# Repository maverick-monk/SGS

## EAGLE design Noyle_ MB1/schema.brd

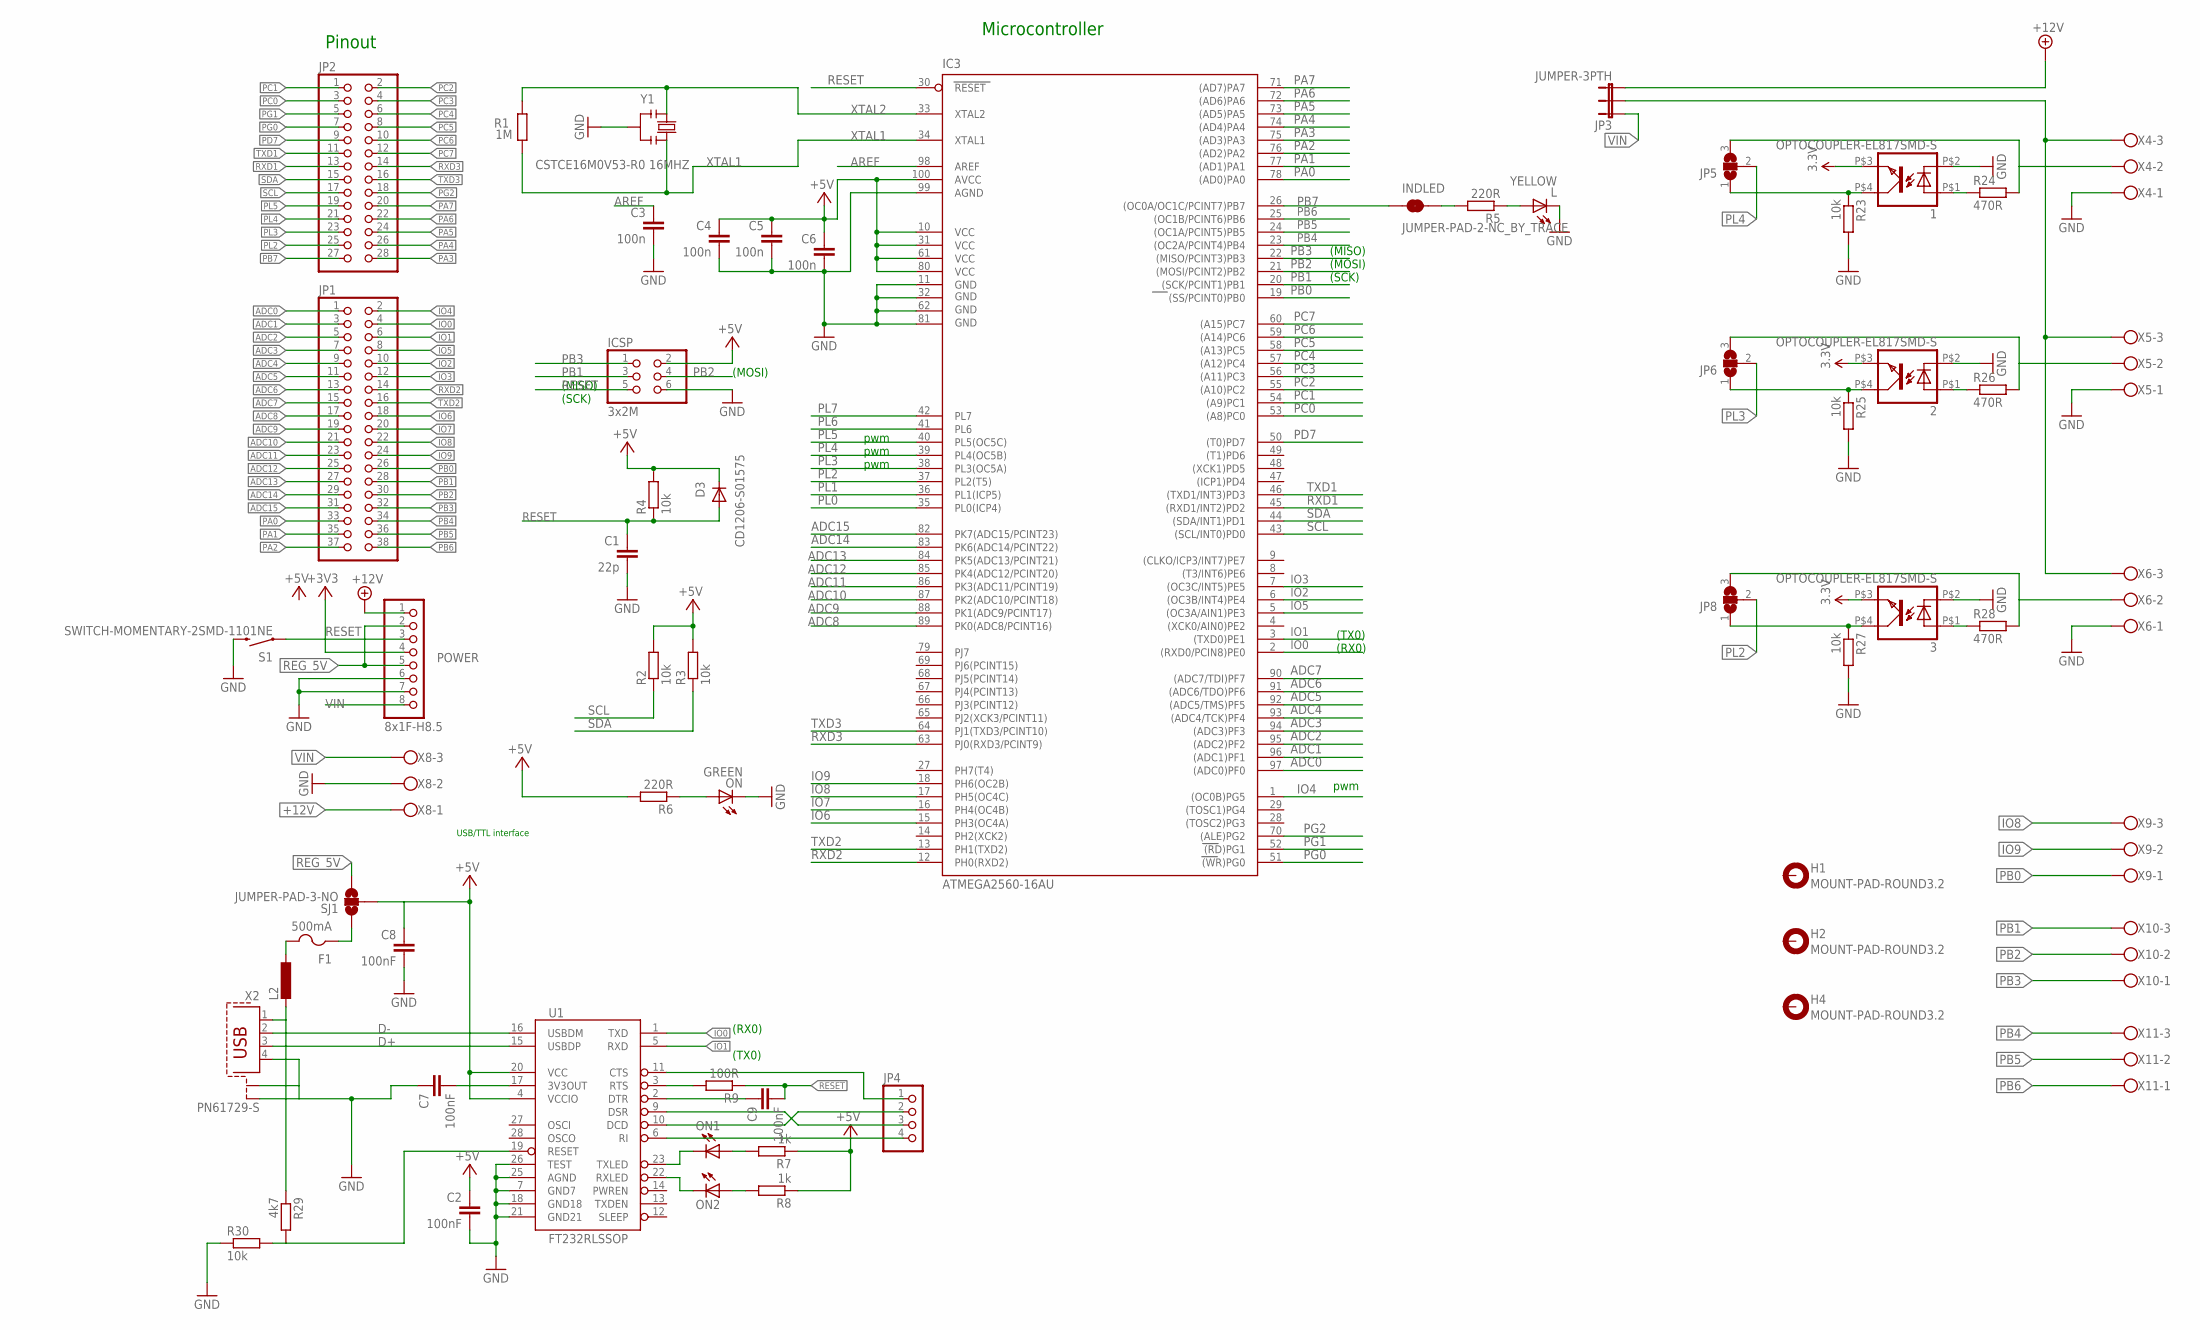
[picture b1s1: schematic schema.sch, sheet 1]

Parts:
1, 2, 3: OPTOCOUPLER-EL817SMD-S; SMD-S
C1: 22p; C0603-ROUND
C2, C7, C8, C9: 100nF; C0603-ROUND
C3, C4, C5, C6: 100n; C0603-ROUND
D3: CD1206-S01575; MINIMELF
F1: 500mA; 1812
H1, H2, H4: MOUNT-PAD-ROUND3.2; 3,2-PAD
IC3: ATMEGA2560-16AU; TQFP100
ICSP: 3x2M; 2X03
INDLED: JUMPER-PAD-2-NC_BY_TRACE; PAD-JUMPER-2-NC_BY_TRACE_YES_SILK
JP1: PINHD-2X19; 2X19
JP2: PINHD-2X14; 2X14
JP3: JUMPER-3PTH; 1X03
JP4: PINHD-1X4; 1X04
JP5, JP6, JP8: SJ2W; SJ_2
L: YELLOW; CHIP-LED0805
L2: L-EUL1812; L1812
ON, ON1, ON2: GREEN; CHIP-LED0805
POWER: 8x1F-H8.5; 1X08
R1: 1M; R0603-ROUND
R2, R3, R4, R23, R25, R27, R30: 10k; R0603
R5, R6: 220R; R0603
R7, R8: 1k; R0603
R9: 100R; R0603
R24, R26, R28: 470R; R0603
R29: 4k7; R0603
S1: SWITCH-MOMENTARY-2SMD-1101NE; TACTILE-SWITCH-1101NE
SJ1: JUMPER-PAD-3-NO; PAD-JUMPER-3-NO_YES_SILK_FULL_BOX_WIDE_SPACING
U1: FT232RLSSOP; SSOP28DB
X2: PN61729-S
X4, X5, X6, X8, X9, X10, X11: W237-103
Y1: CSTCE16M0V53-R0 16MHZ; RESONATOR

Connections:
3.3V: 1.P$3 (3), 2.P$3 (3), 3.P$3 (3), POWER.4; also elsewhere on the board
+5V: C2.1, C4.1, C5.1, C6.1, C8.1, D3.C, IC3.10 (VCC), IC3.31 (VCC1), IC3.61 (VCC2), IC3.80 (VCC3), IC3.100 (AVCC), ICSP.2, R2.2, R3.2, R4.2, R6.2, R7.1, R8.1, SJ1.2, U1.4 (VCCIO), U1.20 (VCC); also elsewhere on the board
+12V: JP3.3, POWER.1, X8.1; also elsewhere on the board
ADC0: IC3.97 ((ADC0)PF0), JP1.1
ADC1: IC3.96 ((ADC1)PF1), JP1.3
ADC2: IC3.95 ((ADC2)PF2), JP1.5
ADC3: IC3.94 ((ADC3)PF3), JP1.7
ADC4: IC3.93 ((ADC4/TCK)PF4), JP1.9
ADC5: IC3.92 ((ADC5/TMS)PF5), JP1.11
ADC6: IC3.91 ((ADC6/TDO)PF6), JP1.13
ADC7: IC3.90 ((ADC7/TDI)PF7), JP1.15
ADC8: IC3.89 (PK0(ADC8/PCINT16)), JP1.17
ADC9: IC3.88 (PK1(ADC9/PCINT17)), JP1.19
ADC10: IC3.87 (PK2(ADC10/PCINT18)), JP1.21
ADC11: IC3.86 (PK3(ADC11/PCINT19)), JP1.23
ADC12: IC3.85 (PK4(ADC12/PCINT20)), JP1.25
ADC13: IC3.84 (PK5(ADC13/PCINT21)), JP1.27
ADC14: IC3.83 (PK6(ADC14/PCINT22)), JP1.29
ADC15: IC3.82 (PK7(ADC15/PCINT23)), JP1.31
AREF: C3.1, IC3.98 (AREF)
D+: U1.15 (USBDP), X2.3
D-: U1.16 (USBDM), X2.2
GND: 1.P$2 (2), 2.P$2 (2), 3.P$2 (2), C1.2, C2.2, C3.2, C4.2, C5.2, C6.2, C7.1, C8.2, IC3.11 (GND), IC3.32 (GND1), IC3.62 (GND2), IC3.81 (GND3), IC3.99 (AGND), ICSP.6, L.C, ON.C, POWER.6, POWER.7, R23.2, R25.2, R27.2, R30.1, S1.2, U1.7 (GND7), U1.18 (GND18), U1.21 (GND21), U1.25 (AGND), U1.26 (TEST), X2.4, X2.S1, X2.S2, X4.1, X5.1, X6.1, X8.2, Y1.2; also elsewhere on the board
IO0: IC3.2 ((RXD0/PCIN8)PE0), JP1.4, U1.1 (TXD)
IO1: IC3.3 ((TXD0)PE1), JP1.6, U1.5 (RXD)
IO2: IC3.6 ((OC3B/INT4)PE4), JP1.10
IO3: IC3.7 ((OC3C/INT5)PE5), JP1.12
IO4: IC3.1 ((OC0B)PG5), JP1.2
IO5: IC3.5 ((OC3A/AIN1)PE3), JP1.8
IO6: IC3.15 (PH3(OC4A)), JP1.18
IO7: IC3.16 (PH4(OC4B)), JP1.20
IO8: IC3.17 (PH5(OC4C)), JP1.22, X9.3
IO9: IC3.18 (PH6(OC2B)), JP1.24, X9.2
unnamed: L.A, R5.1
unnamed: ON1.A, R7.2
unnamed: ON.A, R6.1
unnamed: ON2.A, R8.2
unnamed: C7.2, U1.17 (3V3OUT)
unnamed: L2.2, R29.1, X2.1
unnamed: ON1.C, U1.23 (TXLED)
unnamed: ON2.C, U1.22 (RXLED)
unnamed: R9.2, U1.3 (RTS)
unnamed: C9.1, U1.2 (DTR)
unnamed: JP4.1, U1.11 (CTS)
unnamed: JP4.2, U1.10 (DCD)
unnamed: JP4.3, U1.9 (DSR)
unnamed: JP4.4, U1.6 (RI)
unnamed: INDLED.2, R5.2
unnamed: F1.2, L2.1
unnamed: JP3.2, X4.3, X5.3, X6.3
unnamed: 2.P$4 (4), JP6.1, R25.1
unnamed: 1.P$4 (4), JP5.1, R23.1
unnamed: JP5.3, R24.2, X4.2
unnamed: 1.P$1 (1), R24.1
unnamed: JP6.3, R26.2, X5.2
unnamed: 2.P$1 (1), R26.1
unnamed: R29.2, R30.2, U1.19 (RESET)
unnamed: 3.P$4 (4), JP8.1, R27.1
unnamed: JP8.3, R28.2, X6.2
unnamed: 3.P$1 (1), R28.1
PA0: IC3.78 ((AD0)PA0), JP1.33
PA1: IC3.77 ((AD1)PA1), JP1.35
PA2: IC3.76 ((AD2)PA2), JP1.37
PA3: IC3.75 ((AD3)PA3), JP2.28
PA4: IC3.74 ((AD4)PA4), JP2.26
PA5: IC3.73 ((AD5)PA5), JP2.24
PA6: IC3.72 ((AD6)PA6), JP2.22
PA7: IC3.71 ((AD7)PA7), JP2.20
PB0: IC3.19 ((SS/PCINT0)PB0), JP1.26, X9.1
PB1: IC3.20 ((SCK/PCINT1)PB1), ICSP.3, JP1.28, X10.3
PB2: IC3.21 ((MOSI/PCINT2)PB2), ICSP.4, JP1.30, X10.2
PB3: IC3.22 ((MISO/PCINT3)PB3), ICSP.1, JP1.32, X10.1
PB4: IC3.23 ((OC2A/PCINT4)PB4), JP1.34, X11.3
PB5: IC3.24 ((OC1A/PCINT5)PB5), JP1.36, X11.2
PB6: IC3.25 ((OC1B/PCINT6)PB6), JP1.38, X11.1
PB7: IC3.26 ((OC0A/OC1C/PCINT7)PB7), INDLED.1, JP2.27
PC0: IC3.53 ((A8)PC0), JP2.3
PC1: IC3.54 ((A9)PC1), JP2.1
PC2: IC3.55 ((A10)PC2), JP2.2
PC3: IC3.56 ((A11)PC3), JP2.4
PC4: IC3.57 ((A12)PC4), JP2.6
PC5: IC3.58 ((A13)PC5), JP2.8
PC6: IC3.59 ((A14)PC6), JP2.10
PC7: IC3.60 ((A15)PC7), JP2.12
PD7: IC3.50 ((T0)PD7), JP2.9
PG0: IC3.51 ((WR)PG0), JP2.7
PG1: IC3.52 ((RD)PG1), JP2.5
PG2: IC3.70 ((ALE)PG2), JP2.18
PL0: IC3.35 (PL0(ICP4))
PL1: IC3.36 (PL1(ICP5))
PL2: IC3.37 (PL2(T5)), JP2.25, JP8.2
PL3: IC3.38 (PL3(OC5A)), JP2.23, JP6.2
PL4: IC3.39 (PL4(OC5B)), JP2.21, JP5.2
PL5: IC3.40 (PL5(OC5C)), JP2.19
PL6: IC3.41 (PL6)
PL7: IC3.42 (PL7)
REG_5V: POWER.2, POWER.5, SJ1.3; also elsewhere on the board
RESET: C1.1, C9.2, D3.A, IC3.30 (RESET), ICSP.5, POWER.3, R4.1, R9.1, S1.1
RXD1: IC3.45 ((RXD1/INT2)PD2), JP2.13; also elsewhere on the board
RXD2: IC3.12 (PH0(RXD2)), JP1.14
RXD3: IC3.63 (PJ0(RXD3/PCINT9)), JP2.14; also elsewhere on the board
SCL: IC3.43 ((SCL/INT0)PD0), JP2.17, R2.1
SDA: IC3.44 ((SDA/INT1)PD1), JP2.15, R3.1
TXD1: IC3.46 ((TXD1/INT3)PD3), JP2.11; also elsewhere on the board
TXD2: IC3.13 (PH1(TXD2)), JP1.16
TXD3: IC3.64 (PJ1(TXD3/PCINT10)), JP2.16; also elsewhere on the board
VIN: JP3.1, POWER.8, X8.3; also elsewhere on the board
VUSB: F1.1, SJ1.1
XTAL1: IC3.34 (XTAL1), R1.1, Y1.3
XTAL2: IC3.33 (XTAL2), R1.2, Y1.1

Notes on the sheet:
(SCK)
(MISO)
(MOSI)
pwm
(TX0)
(RX0)
Pinout
Microcontroller
USB/TTL interface

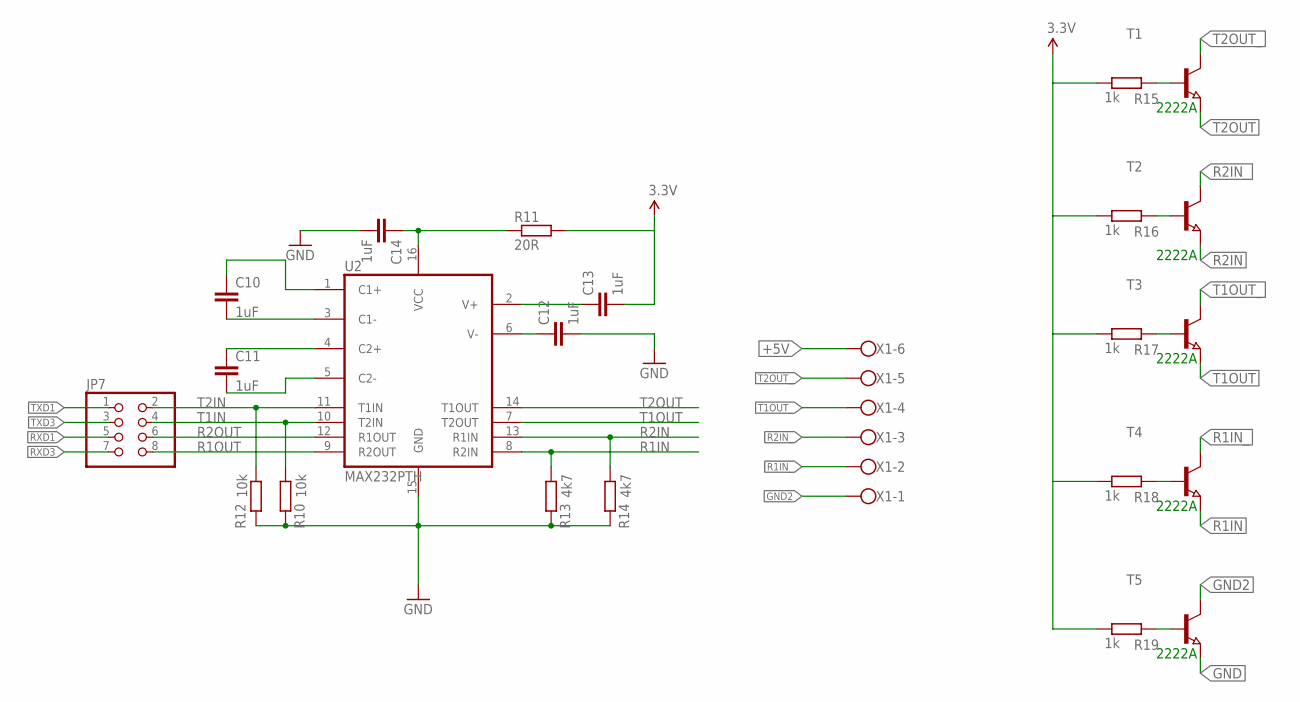
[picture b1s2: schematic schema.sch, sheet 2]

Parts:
C10, C11, C12, C13, C14: 1uF; C0603
JP7: PINHD-2X4; 2X04
R10, R12: 10k; R0603
R11: 20R; R0603
R13, R14: 4k7; R0603
R15, R16, R17, R18, R19: 1k; R0603
T1, T2, T3, T4, T5: NPN-TRANSISTOR_SOT23; SOT23
U2: MAX232PTH; DIL16
X1: W237-6

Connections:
3.3V: C13.2, R11.2, R15.1, R16.1, R17.1, R18.1, R19.1; also elsewhere on the board
+5V: X1.6; also elsewhere on the board
GND: C12.2, C14.2, R10.2, R12.2, R13.2, R14.2, T5.2 (E), U2.15 (GND); also elsewhere on the board
GND2: T5.3 (C), X1.1
unnamed: C10.2, U2.3 (C1-)
unnamed: C10.1, U2.1 (C1+)
unnamed: C11.2, U2.5 (C2-)
unnamed: C11.1, U2.4 (C2+)
unnamed: C12.1, U2.6 (V-)
unnamed: C14.1, R11.1, U2.16 (VCC)
unnamed: C13.1, U2.2 (V+)
unnamed: R15.2, T1.1 (B)
unnamed: R16.2, T2.1 (B)
unnamed: R17.2, T3.1 (B)
unnamed: R18.2, T4.1 (B)
unnamed: R19.2, T5.1 (B)
R1IN: R13.1, T4.2 (E), U2.8 (R2IN)
R1IN_: T4.3 (C), X1.2
R1OUT: JP7.8, U2.9 (R2OUT)
R2IN: R14.1, T2.2 (E), U2.13 (R1IN)
R2IN_: T2.3 (C), X1.3
R2OUT: JP7.6, U2.12 (R1OUT)
RXD1: JP7.5; also elsewhere on the board
RXD3: JP7.7; also elsewhere on the board
T1IN: JP7.4, R10.1, U2.10 (T2IN)
T1OUT: T3.2 (E), U2.7 (T2OUT)
T1OUT_: T3.3 (C), X1.4
T2IN: JP7.2, R12.1, U2.11 (T1IN)
T2OUT: T1.2 (E), U2.14 (T1OUT)
T2OUT_: T1.3 (C), X1.5
TXD1: JP7.1; also elsewhere on the board
TXD3: JP7.3; also elsewhere on the board

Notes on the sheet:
2222A

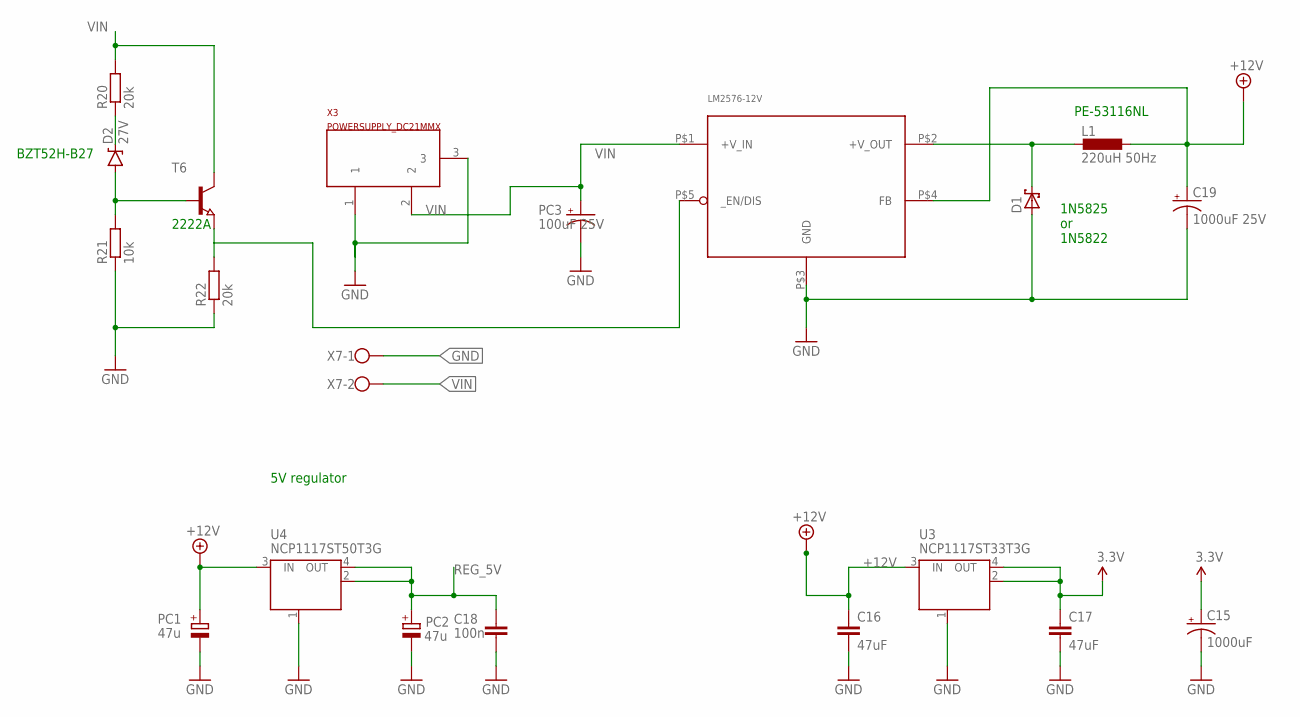
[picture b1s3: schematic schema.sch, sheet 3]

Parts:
C15: 1000uF; E5-6
C16, C17: 47uF; C0603
C18: 100n; C0603-ROUND
C19: 1000uF 25V; E5-6
D1: 1N5908; C4111-15
D2: 27V; SOD-123
L1: 220uH 50Hz; KM-4.0
LM2576-12V: LM2576-T05D; TO220-5_STAGGERED
PC1, PC2: 47u; PANASONIC_D
PC3: 100uF 25V; E5-6
R20, R22: 20k; R0603
R21: 10k; R0603
T6: NPN-TRANSISTOR_SOT23; SOT23
U3: NCP1117ST33T3G; SOT223
U4: NCP1117ST50T3G; SOT223
X3: POWERSUPPLY_DC21MMX; POWERSUPPLY_DC-21MM
X7: W237-102

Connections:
3.3V: C15.+, C17.1, U3.2 (OUT), U3.4 (OUT); also elsewhere on the board
+12V: C16.1, C19.+, L1.P$2 (2), LM2576-12V.P$4 (FB), PC1.+, U3.3 (IN), U4.3 (IN); also elsewhere on the board
GND: C15.-, C16.2, C17.2, C18.1, C19.-, D1.A, LM2576-12V.P$3 (GND), PC1.-, PC2.-, PC3.-, R21.1, R22.1, U3.1 (GND/ADJ), U4.1 (GND/ADJ), X3.1, X3.3, X7.1; also elsewhere on the board
unnamed: D1.C, L1.P$1 (1), LM2576-12V.P$2 (+V_OUT)
unnamed: D2.A, R21.2, T6.1 (B)
unnamed: D2.C, R20.1
unnamed: LM2576-12V.P$5 (_EN/DIS), R22.2, T6.2 (E)
REG_5V: C18.2, PC2.+, U4.2 (OUT), U4.4 (OUT); also elsewhere on the board
VIN: LM2576-12V.P$1 (+V_IN), PC3.+, R20.2, T6.3 (C), X3.2, X7.2; also elsewhere on the board

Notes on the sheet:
5V regulator
1N5825 or 1N5822
PE-53116NL
BZT52H-B27
2222A

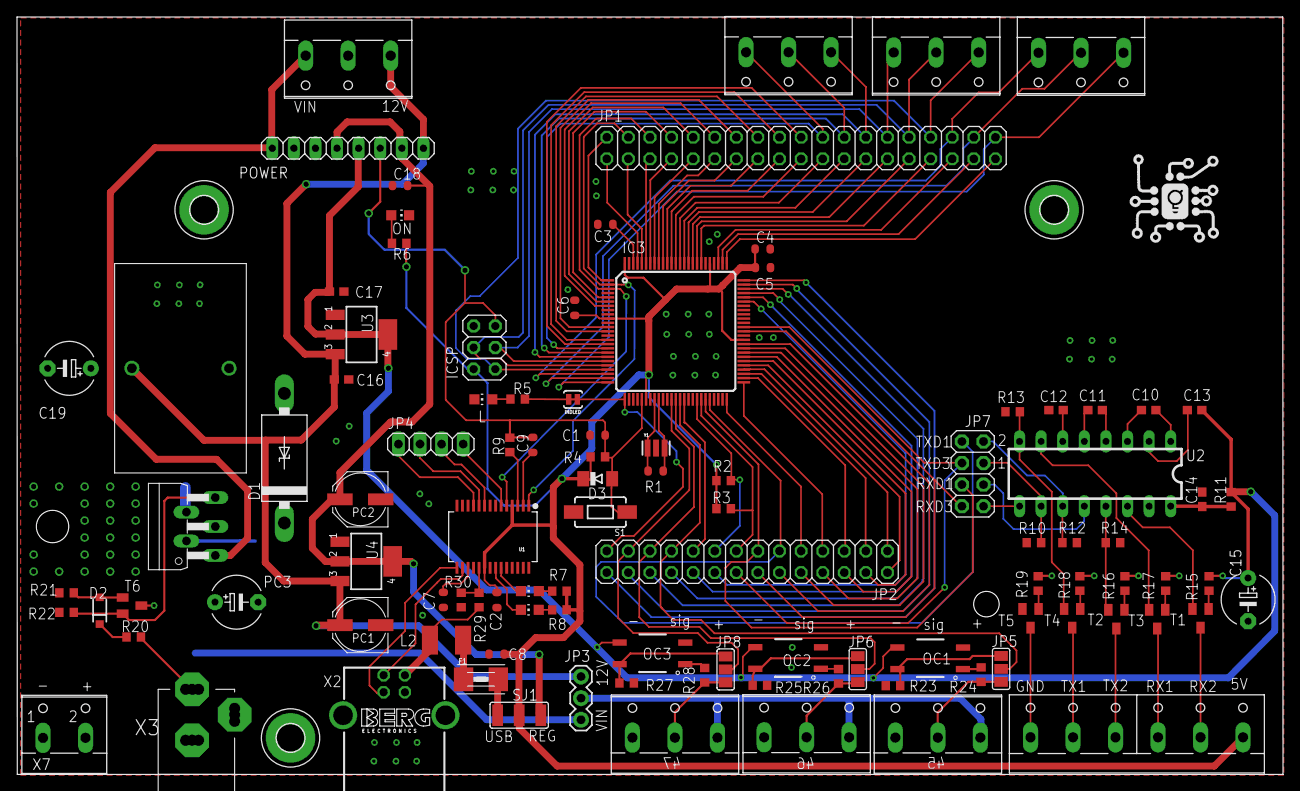
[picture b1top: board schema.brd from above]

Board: 2 copper layers, 148.8 x 89.0 mm, 105 parts (0 on the bottom side), 135 nets.

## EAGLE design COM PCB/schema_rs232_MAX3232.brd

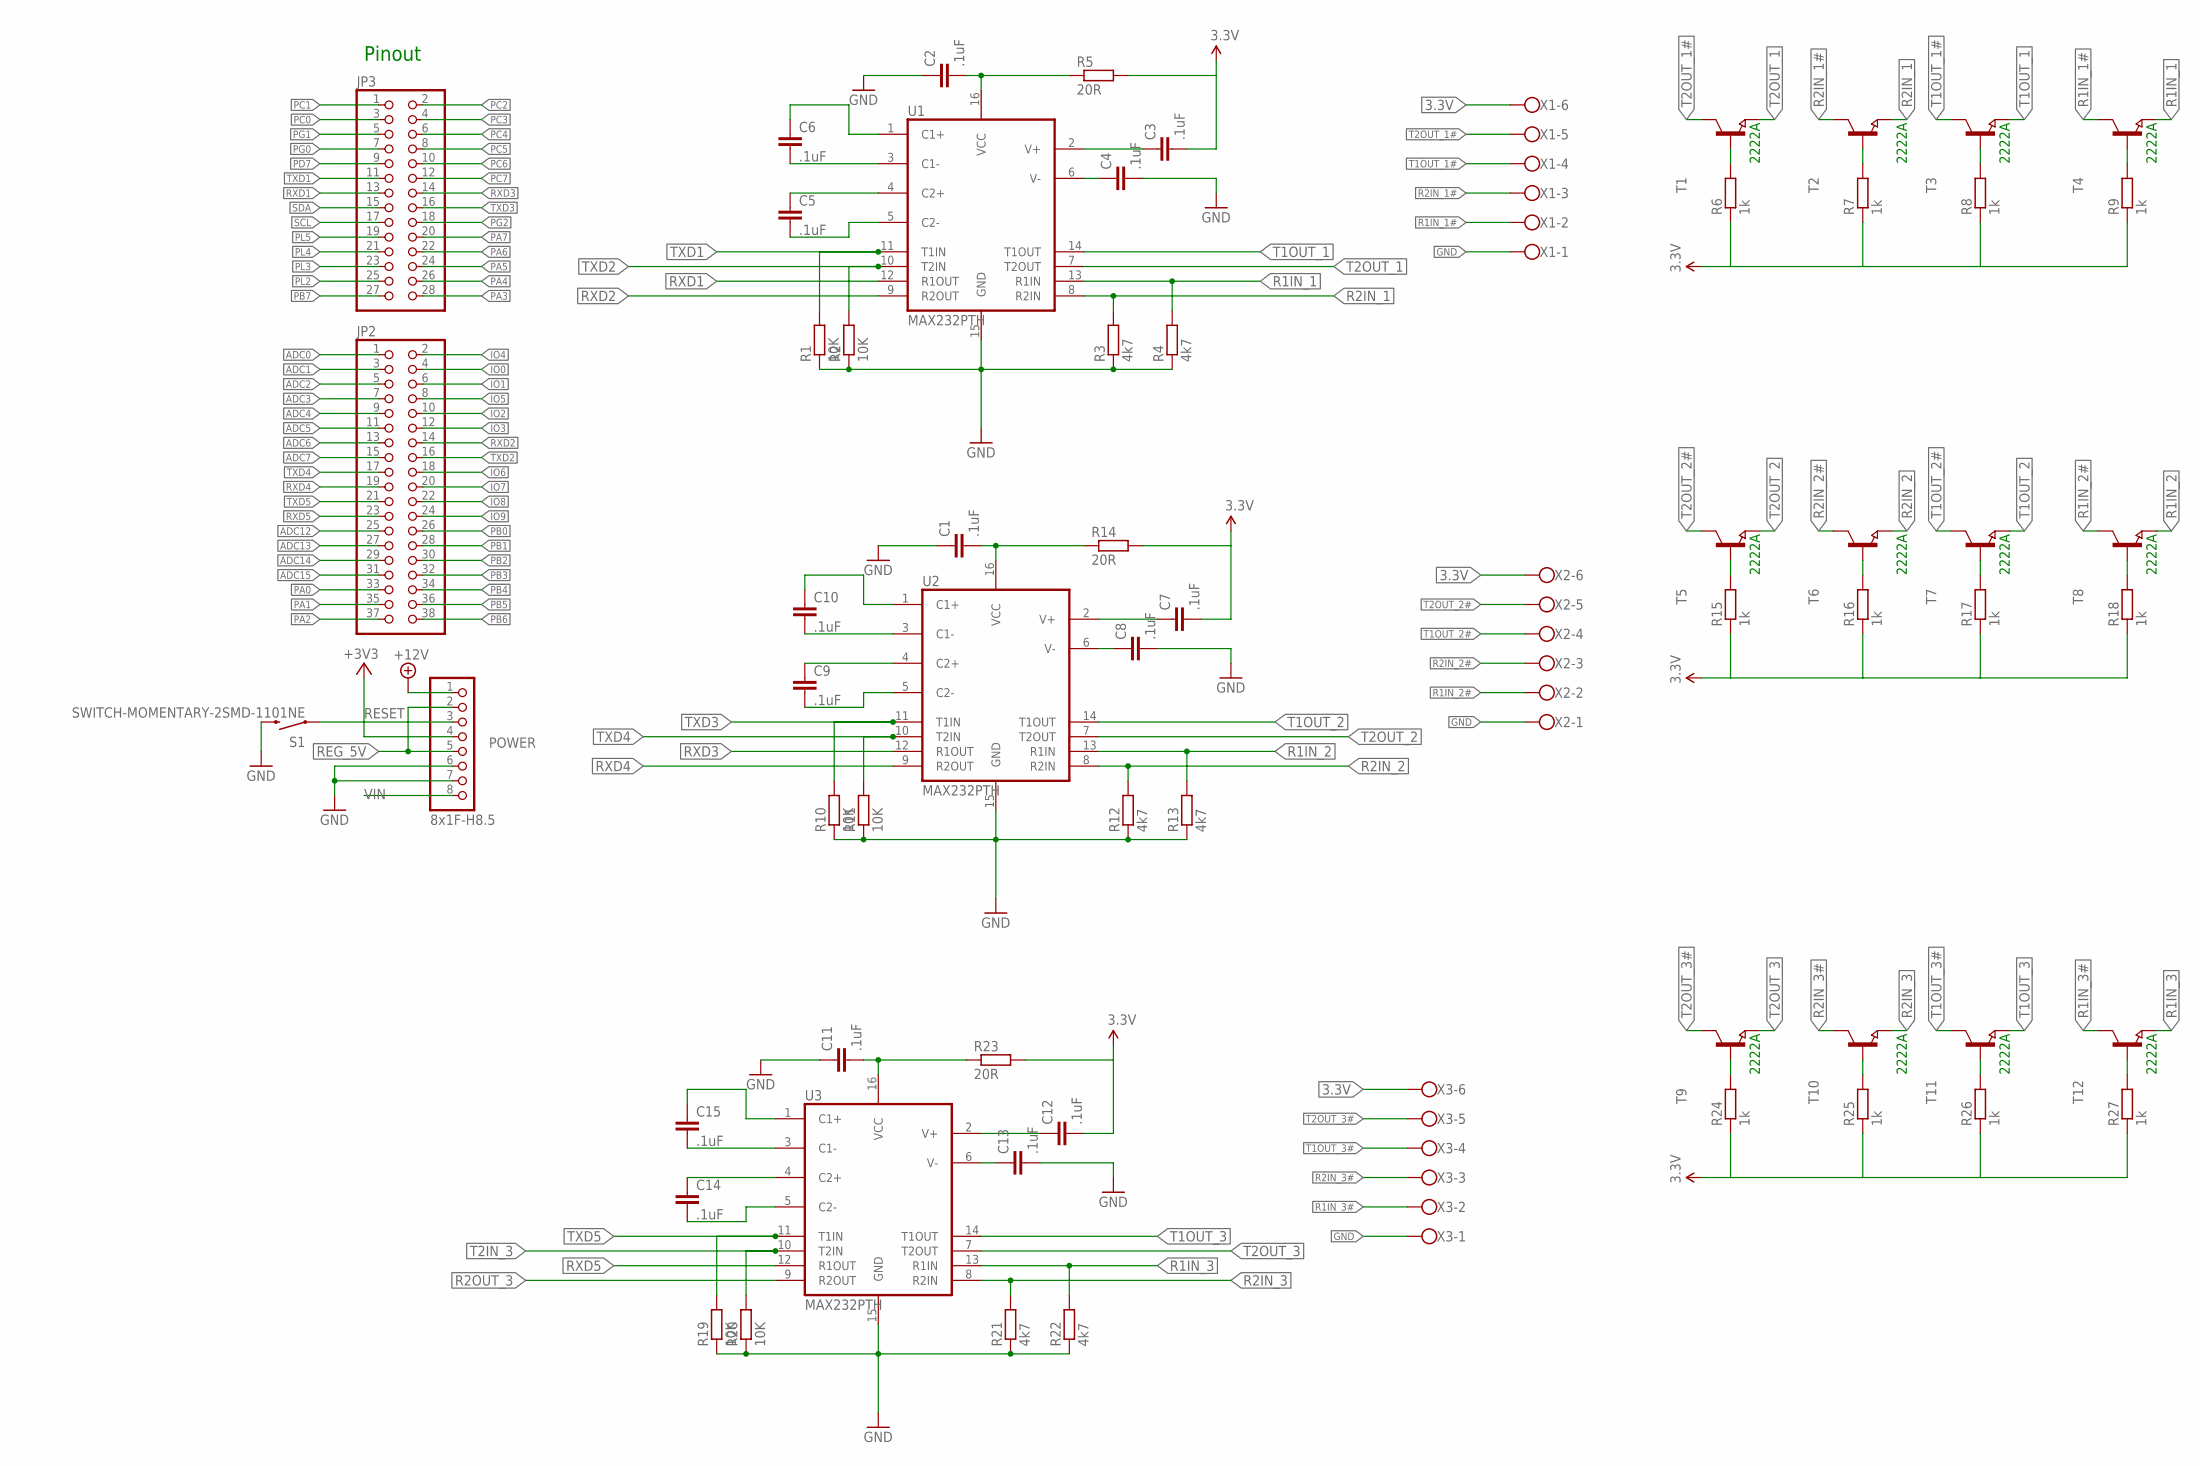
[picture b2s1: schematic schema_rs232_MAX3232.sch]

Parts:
C1, C2, C3, C4, C5, C6, C7, C8, C9, C10, C11, C12, C13, C14, C15: .1uF; C0805
JP2: PINHD-2X19; 2X19
JP3: PINHD-2X14; 2X14
POWER: 8x1F-H8.5; 1X08
R1, R2, R10, R11, R19, R20: 10K; R0805
R3, R4, R12, R13, R21, R22: 4k7; R0805
R5, R14, R23: 20R; R0805
R6, R7, R8, R9, R15, R16, R17, R18, R24, R25, R26, R27: 1k; R0805
S1: SWITCH-MOMENTARY-2SMD-1101NE; TACTILE-SWITCH-1101NE
T1, T2, T3, T4, T5, T6, T7, T8, T9, T10, T11, T12: NPN-TRANSISTOR_SOT23; SOT23
U1, U2, U3: MAX232PTH; DIL16
X1, X2, X3: W237-6

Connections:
3.3V: C3.2, C7.2, C12.2, POWER.4, R5.2, R6.1, R7.1, R8.1, R9.1, R14.2, R15.1, R16.1, R17.1, R18.1, R23.2, R24.1, R25.1, R26.1, R27.1, X1.6, X2.6, X3.6
+12V: POWER.1
ADC0: JP2.1
ADC1: JP2.3
ADC2: JP2.5
ADC3: JP2.7
ADC4: JP2.9
ADC5: JP2.11
ADC6: JP2.13
ADC7: JP2.15
ADC12: JP2.25
ADC13: JP2.27
ADC14: JP2.29
ADC15: JP2.31
GND: C1.1, C2.1, C4.2, C8.2, C11.1, C13.2, POWER.6, POWER.7, R1.1, R2.1, R3.1, R4.1, R10.1, R11.1, R12.1, R13.1, R19.1, R20.1, R21.1, R22.1, S1.2, U1.15 (GND), U2.15 (GND), U3.15 (GND), X1.1, X2.1, X3.1
IO0: JP2.4
IO1: JP2.6
IO2: JP2.10
IO3: JP2.12
IO4: JP2.2
IO5: JP2.8
IO6: JP2.18
IO7: JP2.20
IO8: JP2.22
IO9: JP2.24
unnamed: C10.2, U2.3 (C1-)
unnamed: C10.1, U2.1 (C1+)
unnamed: C9.2, U2.5 (C2-)
unnamed: C9.1, U2.4 (C2+)
unnamed: C8.1, U2.6 (V-)
unnamed: C1.2, R14.1, U2.16 (VCC)
unnamed: C7.1, U2.2 (V+)
unnamed: R15.2, T5.1 (B)
unnamed: R16.2, T6.1 (B)
unnamed: R17.2, T7.1 (B)
unnamed: R18.2, T8.1 (B)
unnamed: C15.2, U3.3 (C1-)
unnamed: C15.1, U3.1 (C1+)
unnamed: C14.2, U3.5 (C2-)
unnamed: C6.2, U1.3 (C1-)
unnamed: C6.1, U1.1 (C1+)
unnamed: C5.2, U1.5 (C2-)
unnamed: C5.1, U1.4 (C2+)
unnamed: C4.1, U1.6 (V-)
unnamed: C2.2, R5.1, U1.16 (VCC)
unnamed: C3.1, U1.2 (V+)
unnamed: R6.2, T1.1 (B)
unnamed: R7.2, T2.1 (B)
unnamed: R8.2, T3.1 (B)
unnamed: R9.2, T4.1 (B)
unnamed: C14.1, U3.4 (C2+)
unnamed: C13.1, U3.6 (V-)
unnamed: C11.2, R23.1, U3.16 (VCC)
unnamed: C12.1, U3.2 (V+)
unnamed: R24.2, T9.1 (B)
unnamed: R25.2, T10.1 (B)
unnamed: R26.2, T11.1 (B)
unnamed: R27.2, T12.1 (B)
PA0: JP2.33
PA1: JP2.35
PA2: JP2.37
PA3: JP3.28
PA4: JP3.26
PA5: JP3.24
PA6: JP3.22
PA7: JP3.20
PB0: JP2.26
PB1: JP2.28
PB2: JP2.30
PB3: JP2.32
PB4: JP2.34
PB5: JP2.36
PB6: JP2.38
PB7: JP3.27
PC0: JP3.3
PC1: JP3.1
PC2: JP3.2
PC3: JP3.4
PC4: JP3.6
PC5: JP3.8
PC6: JP3.10
PC7: JP3.12
PD7: JP3.9
PG0: JP3.7
PG1: JP3.5
PG2: JP3.18
PL2: JP3.25
PL3: JP3.23
PL4: JP3.21
PL5: JP3.19
R1IN_1: R4.2, T4.2 (E), U1.13 (R1IN)
R1IN_1#: T4.3 (C), X1.2
R1IN_2: R13.2, T8.2 (E), U2.13 (R1IN)
R1IN_2#: T8.3 (C), X2.2
R1IN_3: R22.2, T12.2 (E), U3.13 (R1IN)
R1IN_3#: T12.3 (C), X3.2
R2IN_1: R3.2, T2.2 (E), U1.8 (R2IN)
R2IN_1#: T2.3 (C), X1.3
R2IN_2: R12.2, T6.2 (E), U2.8 (R2IN)
R2IN_2#: T6.3 (C), X2.3
R2IN_3: R21.2, T10.2 (E), U3.8 (R2IN)
R2IN_3#: T10.3 (C), X3.3
R2OUT_3: U3.9 (R2OUT)
REG_5V: POWER.2, POWER.5
RESET: POWER.3, S1.1
RXD1: JP3.13, U1.12 (R1OUT)
RXD2: JP2.14, U1.9 (R2OUT)
RXD3: JP3.14, U2.12 (R1OUT)
RXD4: JP2.19, U2.9 (R2OUT)
RXD5: JP2.23, U3.12 (R1OUT)
SCL: JP3.17
SDA: JP3.15
T1OUT_1: T3.2 (E), U1.14 (T1OUT)
T1OUT_1#: T3.3 (C), X1.4
T1OUT_2: T7.2 (E), U2.14 (T1OUT)
T1OUT_2#: T7.3 (C), X2.4
T1OUT_3: T11.2 (E), U3.14 (T1OUT)
T1OUT_3#: T11.3 (C), X3.4
T2IN_3: R20.2, U3.10 (T2IN)
T2OUT_1: T1.2 (E), U1.7 (T2OUT)
T2OUT_1#: T1.3 (C), X1.5
T2OUT_2: T5.2 (E), U2.7 (T2OUT)
T2OUT_2#: T5.3 (C), X2.5
T2OUT_3: T9.2 (E), U3.7 (T2OUT)
T2OUT_3#: T9.3 (C), X3.5
TXD1: JP3.11, R1.2, U1.11 (T1IN)
TXD2: JP2.16, R2.2, U1.10 (T2IN)
TXD3: JP3.16, R10.2, U2.11 (T1IN)
TXD4: JP2.17, R11.2, U2.10 (T2IN)
TXD5: JP2.21, R19.2, U3.11 (T1IN)
VIN: POWER.8

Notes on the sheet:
Pinout
2222A

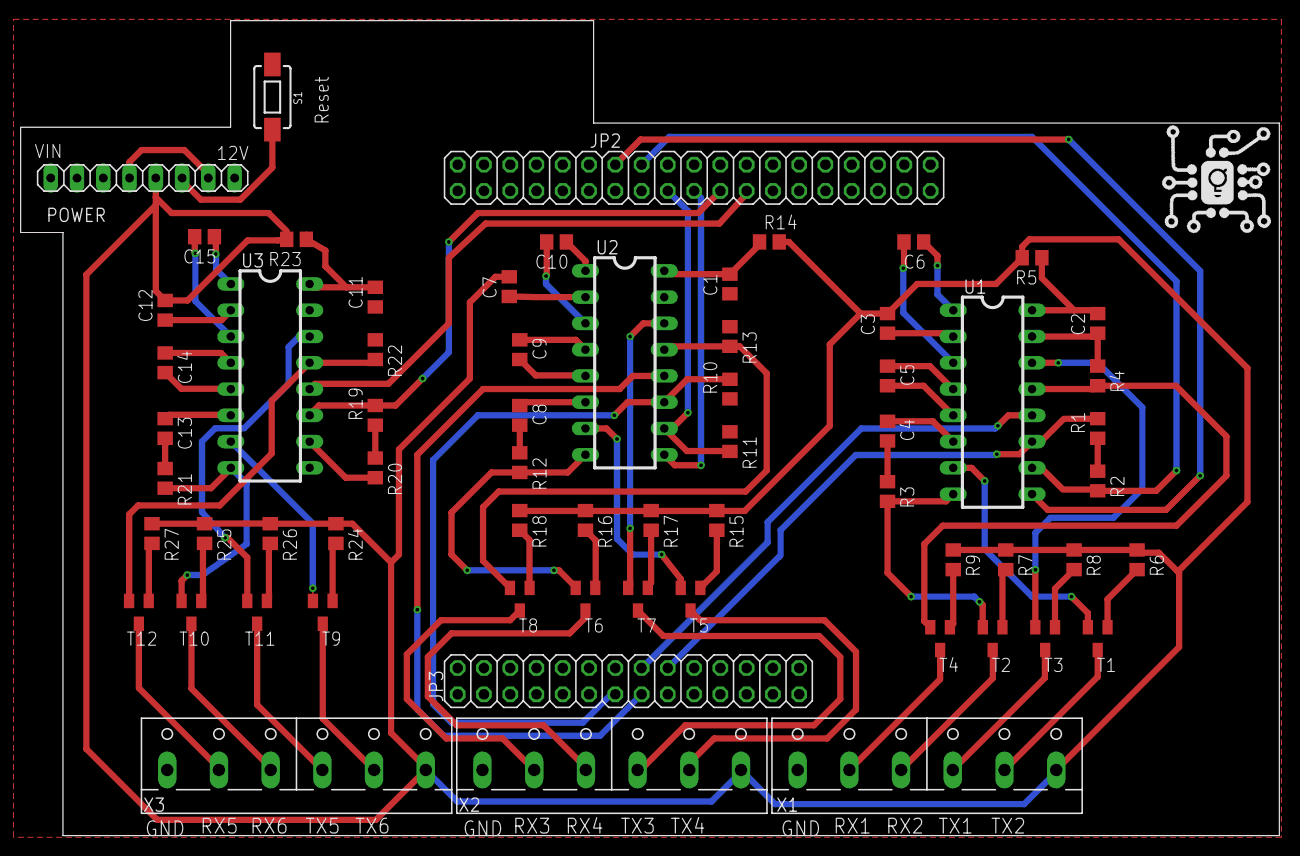
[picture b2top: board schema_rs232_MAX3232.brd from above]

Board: 2 copper layers, 121.7 x 78.8 mm, 64 parts (0 on the bottom side), 72 nets.

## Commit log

2021-08-24 added project files

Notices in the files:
parts and their libraries:
SparkFun-DigitalIC: Licensing: Creative Commons ShareAlike 4.0 International - https://creativecommons.org/licenses/by-sa/4.0
